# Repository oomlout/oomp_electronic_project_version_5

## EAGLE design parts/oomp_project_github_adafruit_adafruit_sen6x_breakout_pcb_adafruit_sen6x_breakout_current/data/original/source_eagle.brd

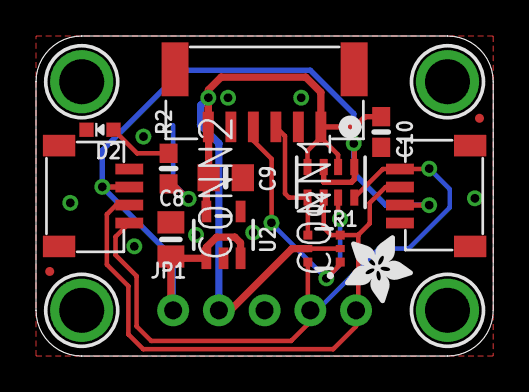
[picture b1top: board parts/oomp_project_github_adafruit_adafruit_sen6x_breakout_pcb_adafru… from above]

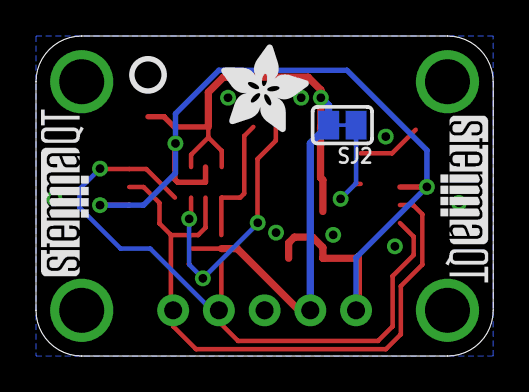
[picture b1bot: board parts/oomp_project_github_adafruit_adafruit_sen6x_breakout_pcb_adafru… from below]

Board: 2 copper layers, 25.4 x 17.8 mm, 35 parts (8 on the bottom side), 9 nets.

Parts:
C8, C9: 10uF; 0805-NO
C10: 0.1uF; 0603-NO
CONN1, CONN2: STEMMA_I2C_QT; JST_SH4
D2: GREEN; CHIPLED_0603_NOOUTLINE
FID1, FID2: FIDUCIAL_0.5MM
JP1: 1X05_ROUND_70
PLABEL14: PLABEL14
PLABEL15: PLABEL15
PLABEL16: PLABEL16
PLABEL17: PLABEL17
PLABEL18: PLABEL18
PLABEL19: PLABEL19
PLABEL20: PLABEL20
PLABEL21: PLABEL21
PLABEL22: PLABEL22
PLABEL23: PLABEL23
PLABEL24: PLABEL24
Q2: BSS138; SOT363
R1: 10K Pack; RESPACK_4X0603
R2: 10K; 0603-NO
SJ2: SOLDERJUMPER_CLOSEDWIRE
U2: AP2127K-3.3; SOT23-5
U$2: ADAFRUIT_5MM
U$35, U$36, U$38, U$39: MOUNTINGHOLE2.5; MOUNTINGHOLE_2.5_PLATED
U$41: ADAFRUIT_3.5MM
U$42: PCBFEAT-REV-040
U$43, U$44: STEMMAQT
X1: SM06B-GHS-TB; CONN_SM06B-GHS-TB_JST

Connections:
3.3V: C9.1, C10.1, JP1.2, Q2.2, Q2.5, R1.2, R1.4, SJ2.2, U2.5, X1.1, X1.6
GND: C8.2, C9.2, C10.2, CONN1.1, CONN1.MT1, CONN1.MT2, CONN2.1, CONN2.MT1, CONN2.MT2, D2.C, JP1.3, U2.2, X1.2, X1.5
unnamed: D2.A, R2.2
unnamed: R2.1, SJ2.1
SCL: CONN1.4, CONN2.4, JP1.4, Q2.6, R1.8
SCL_3V: Q2.1, R1.7, X1.4
SDA: CONN1.3, CONN2.3, JP1.5, Q2.3, R1.6
SDA_3V: Q2.4, R1.5, X1.3
VCC: C8.1, CONN1.2, CONN2.2, JP1.1, R1.1, R1.3, U2.1, U2.3

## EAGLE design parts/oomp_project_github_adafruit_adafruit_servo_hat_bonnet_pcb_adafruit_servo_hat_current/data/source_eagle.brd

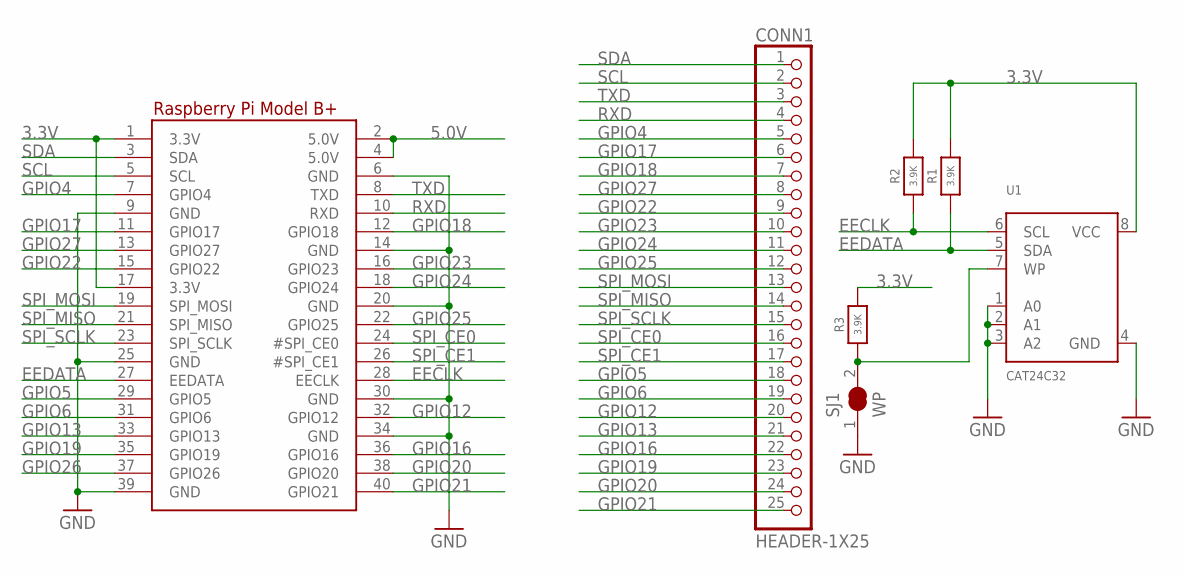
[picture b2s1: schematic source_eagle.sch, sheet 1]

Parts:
CONN1: HEADER-1X25; 1X25_ROUND_70MIL
R1, R2, R3: 3.9K; 0805-NO
RPI1: RASPBERRYPI_BPLUS_HATSLOTS; PI_HAT_SLOTS
SJ1: WP; SOLDERJUMPER_CLOSEDWIRE
U1: CAT24C32; SOIC8_150MIL

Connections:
3.3V: R1.2, R2.2, R3.2, RPI1.1 (3.3V), RPI1.17 (3.3V), U1.8 (VCC); also elsewhere on the board
5.0V: RPI1.2 (5.0V), RPI1.4 (5.0V)
EECLK: R2.1, RPI1.28 (EECLK), U1.6 (SCL)
EEDATA: R1.1, RPI1.27 (EEDATA), U1.5 (SDA)
GND: RPI1.6 (GND), RPI1.9 (GND), RPI1.14 (GND), RPI1.20 (GND), RPI1.25 (GND), RPI1.30 (GND), RPI1.34 (GND), RPI1.39 (GND), SJ1.1, U1.1 (A0), U1.2 (A1), U1.3 (A2), U1.4 (GND); also elsewhere on the board
GPIO4: CONN1.5, RPI1.7 (GPIO4)
GPIO5: CONN1.18, RPI1.29 (GPIO5)
GPIO6: CONN1.19, RPI1.31 (GPIO6)
GPIO12: CONN1.20, RPI1.32 (GPIO12)
GPIO13: CONN1.21, RPI1.33 (GPIO13)
GPIO16: CONN1.22, RPI1.36 (GPIO16)
GPIO17: CONN1.6, RPI1.11 (GPIO17)
GPIO18: CONN1.7, RPI1.12 (GPIO18)
GPIO19: CONN1.23, RPI1.35 (GPIO19)
GPIO20: CONN1.24, RPI1.38 (GPIO20)
GPIO21: CONN1.25, RPI1.40 (GPIO21)
GPIO22: CONN1.9, RPI1.15 (GPIO22)
GPIO23: CONN1.10, RPI1.16 (GPIO23)
GPIO24: CONN1.11, RPI1.18 (GPIO24)
GPIO25: CONN1.12, RPI1.22 (GPIO25)
GPIO26: RPI1.37 (GPIO26)
GPIO27: CONN1.8, RPI1.13 (GPIO27)
unnamed: R3.1, SJ1.2, U1.7 (WP)
RXD: CONN1.4, RPI1.10 (RXD)
SCL: CONN1.2, RPI1.5 (SCL); also elsewhere on the board
SDA: CONN1.1, RPI1.3 (SDA); also elsewhere on the board
SPI_CE0: CONN1.16, RPI1.24 (#SPI_CE0)
SPI_CE1: CONN1.17, RPI1.26 (#SPI_CE1)
SPI_MISO: CONN1.14, RPI1.21 (SPI_MISO)
SPI_MOSI: CONN1.13, RPI1.19 (SPI_MOSI)
SPI_SCLK: CONN1.15, RPI1.23 (SPI_SCLK)
TXD: CONN1.3, RPI1.8 (TXD)

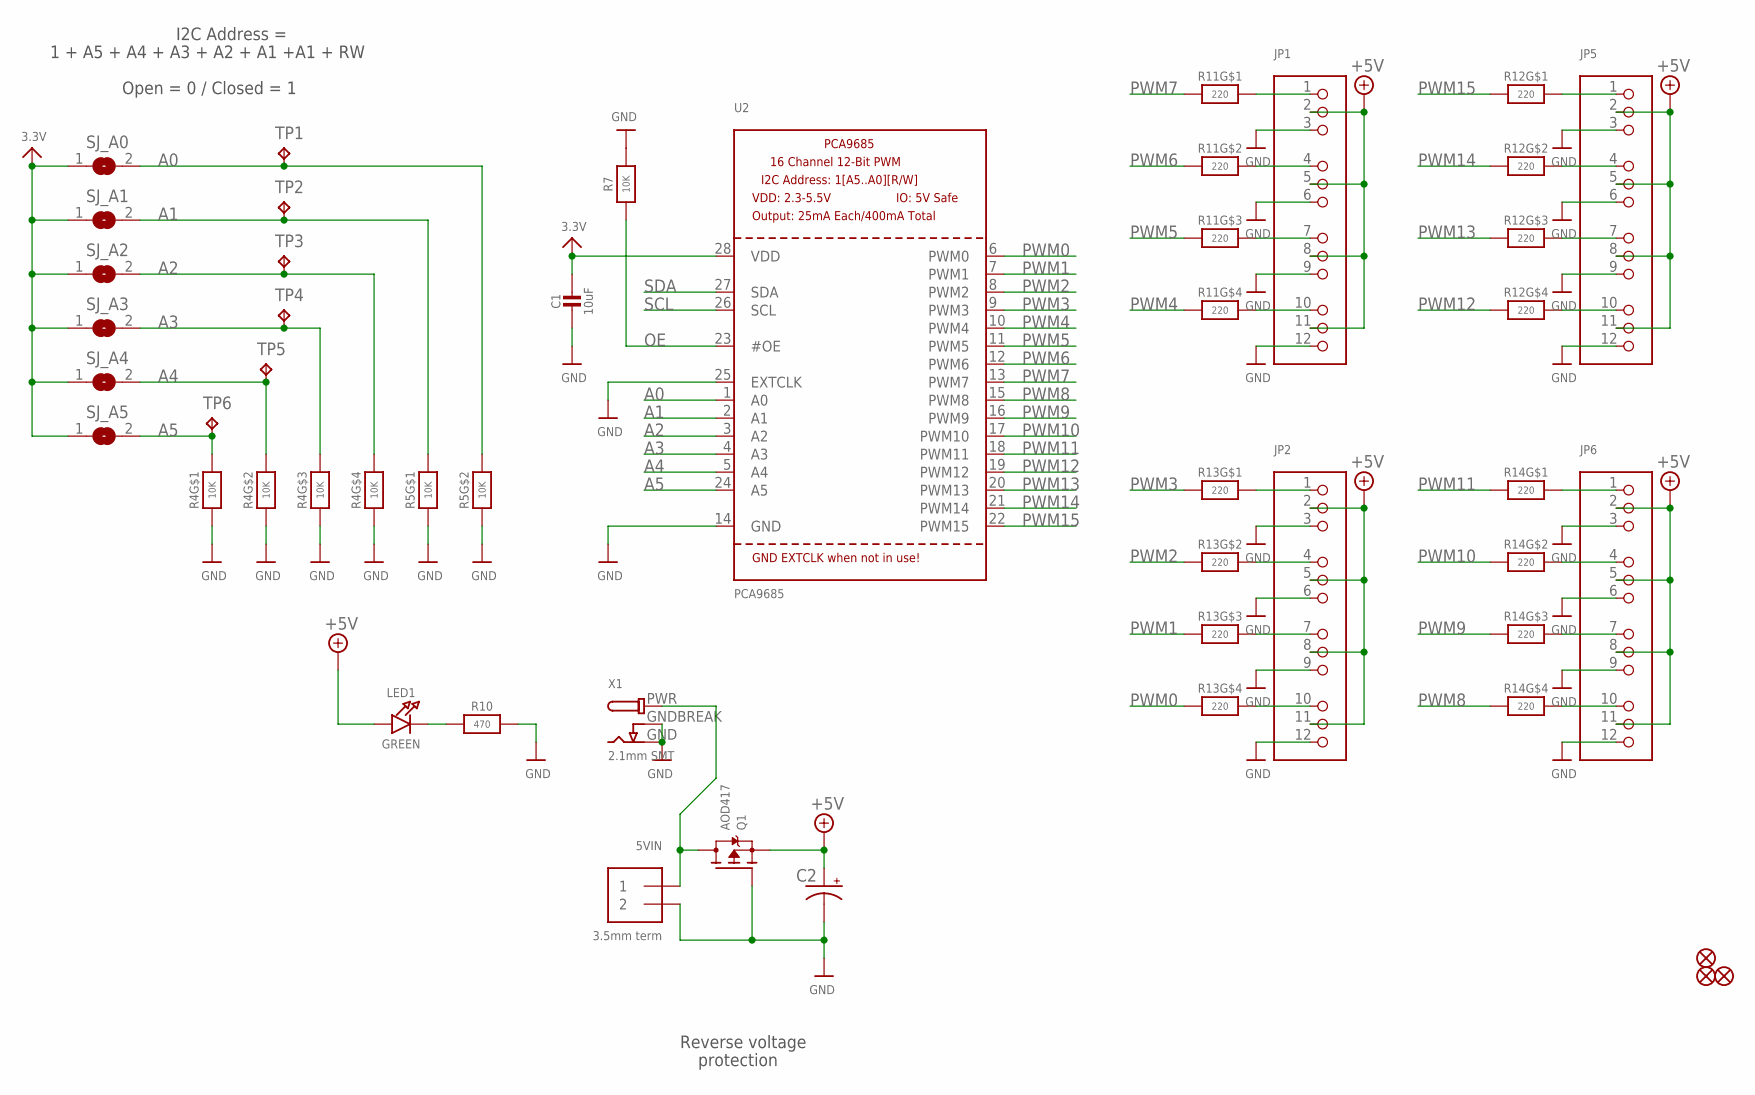
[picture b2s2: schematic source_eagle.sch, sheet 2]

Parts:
5VIN: 3.5mm term; TERMBLOCK_1X2-3.5MM
C1: 10uF; 0805-NO
C2: CPOL-USE3.5-8; E3,5-8
FID1, FID2, FID3: FIDUCIAL""; FIDUCIAL_1MM
JP1, JP2, JP5, JP6: HEADER-3X04; 3X04
LED1: GREEN; CHIPLED_0805_NOOUTLINE
Q1: AOD417; TO252
R4, R5: 10K; RESPACK_4X0603
R7: 10K; 0805-NO
R10: 470; _0805MP
R11, R12, R13, R14: 220; RESPACK_4X0603
SJ_A0, SJ_A1, SJ_A2, SJ_A3, SJ_A4, SJ_A5: SOLDERJUMPERREFLOW_NOPASTE; SOLDERJUMPER_REFLOW_NOPASTE
TP1, TP2, TP3, TP4, TP5, TP6: TPB1,27; B1,27
U2: PCA9685; TSSOP28
X1: 2.1mm SMT; DCJACK_2MM_SMT

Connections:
3.3V: C1.1, SJ_A0.1, SJ_A1.1, SJ_A2.1, SJ_A3.1, SJ_A4.1, SJ_A5.1, U2.28 (VDD); also elsewhere on the board
+5V: C2.+, JP1.2, JP1.5, JP1.8, JP1.11, JP2.2, JP2.5, JP2.8, JP2.11, JP5.2, JP5.5, JP5.8, JP5.11, JP6.2, JP6.5, JP6.8, JP6.11, LED1.A, Q1.2 (S)
A0: R5.7 (2), SJ_A0.2, TP1.TP, U2.1 (A0)
A1: R5.8 (2), SJ_A1.2, TP2.TP, U2.2 (A1)
A2: R4.5 (2), SJ_A2.2, TP3.TP, U2.3 (A2)
A3: R4.6 (2), SJ_A3.2, TP4.TP, U2.4 (A3)
A4: R4.7 (2), SJ_A4.2, TP5.TP, U2.5 (A4)
A5: R4.8 (2), SJ_A5.2, TP6.TP, U2.24 (A5)
GND: 5VIN.2, C1.2, C2.-, JP1.3, JP1.6, JP1.9, JP1.12, JP2.3, JP2.6, JP2.9, JP2.12, JP5.3, JP5.6, JP5.9, JP5.12, JP6.3, JP6.6, JP6.9, JP6.12, Q1.1 (G), R4.1, R4.2 (1), R4.3 (1), R4.4 (1), R5.1, R5.2 (1), R7.2, R10.2, U2.14 (GND), U2.25 (EXTCLK), X1.GND, X1.GNDBREAK; also elsewhere on the board
unnamed: LED1.C, R10.1
unnamed: JP1.4, R11.7 (2)
unnamed: JP1.1, R11.8 (2)
unnamed: JP1.7, R11.6 (2)
unnamed: JP1.10, R11.5 (2)
unnamed: JP2.1, R13.8 (2)
unnamed: JP2.4, R13.7 (2)
unnamed: JP2.7, R13.6 (2)
unnamed: JP2.10, R13.5 (2)
unnamed: JP6.10, R14.5 (2)
unnamed: JP6.7, R14.6 (2)
unnamed: JP6.4, R14.7 (2)
unnamed: JP6.1, R14.8 (2)
unnamed: JP5.10, R12.5 (2)
unnamed: JP5.7, R12.6 (2)
unnamed: JP5.4, R12.7 (2)
unnamed: JP5.1, R12.8 (2)
OE: R7.1, U2.23 (#OE)
PWM0: R13.4 (1), U2.6 (PWM0)
PWM1: R13.3 (1), U2.7 (PWM1)
PWM2: R13.2 (1), U2.8 (PWM2)
PWM3: R13.1, U2.9 (PWM3)
PWM4: R11.4 (1), U2.10 (PWM4)
PWM5: R11.3 (1), U2.11 (PWM5)
PWM6: R11.2 (1), U2.12 (PWM6)
PWM7: R11.1, U2.13 (PWM7)
PWM8: R14.4 (1), U2.15 (PWM8)
PWM9: R14.3 (1), U2.16 (PWM9)
PWM10: R14.2 (1), U2.17 (PWM10)
PWM11: R14.1, U2.18 (PWM11)
PWM12: R12.4 (1), U2.19 (PWM12)
PWM13: R12.3 (1), U2.20 (PWM13)
PWM14: R12.2 (1), U2.21 (PWM14)
PWM15: R12.1, U2.22 (PWM15)
PWRIN: 5VIN.1, Q1.3 (D), X1.PWR
SCL: U2.26 (SCL); also elsewhere on the board
SDA: U2.27 (SDA); also elsewhere on the board

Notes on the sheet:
Reverse voltage
protection
1 + A5 + A4 + A3 + A2 + A1 +A1 + RW
I2C Address =
Open = 0 / Closed = 1

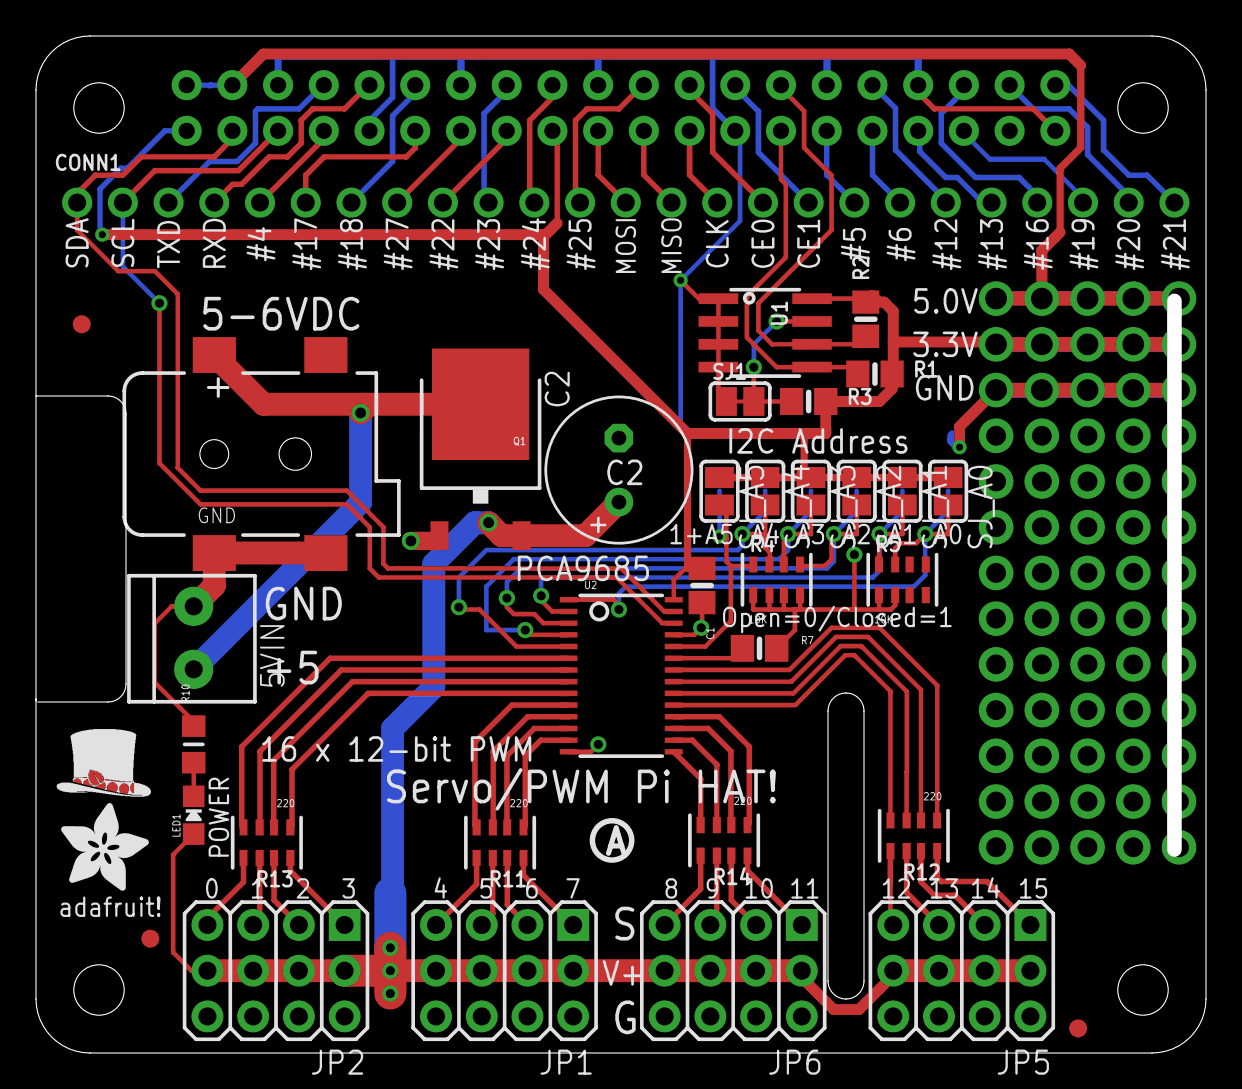
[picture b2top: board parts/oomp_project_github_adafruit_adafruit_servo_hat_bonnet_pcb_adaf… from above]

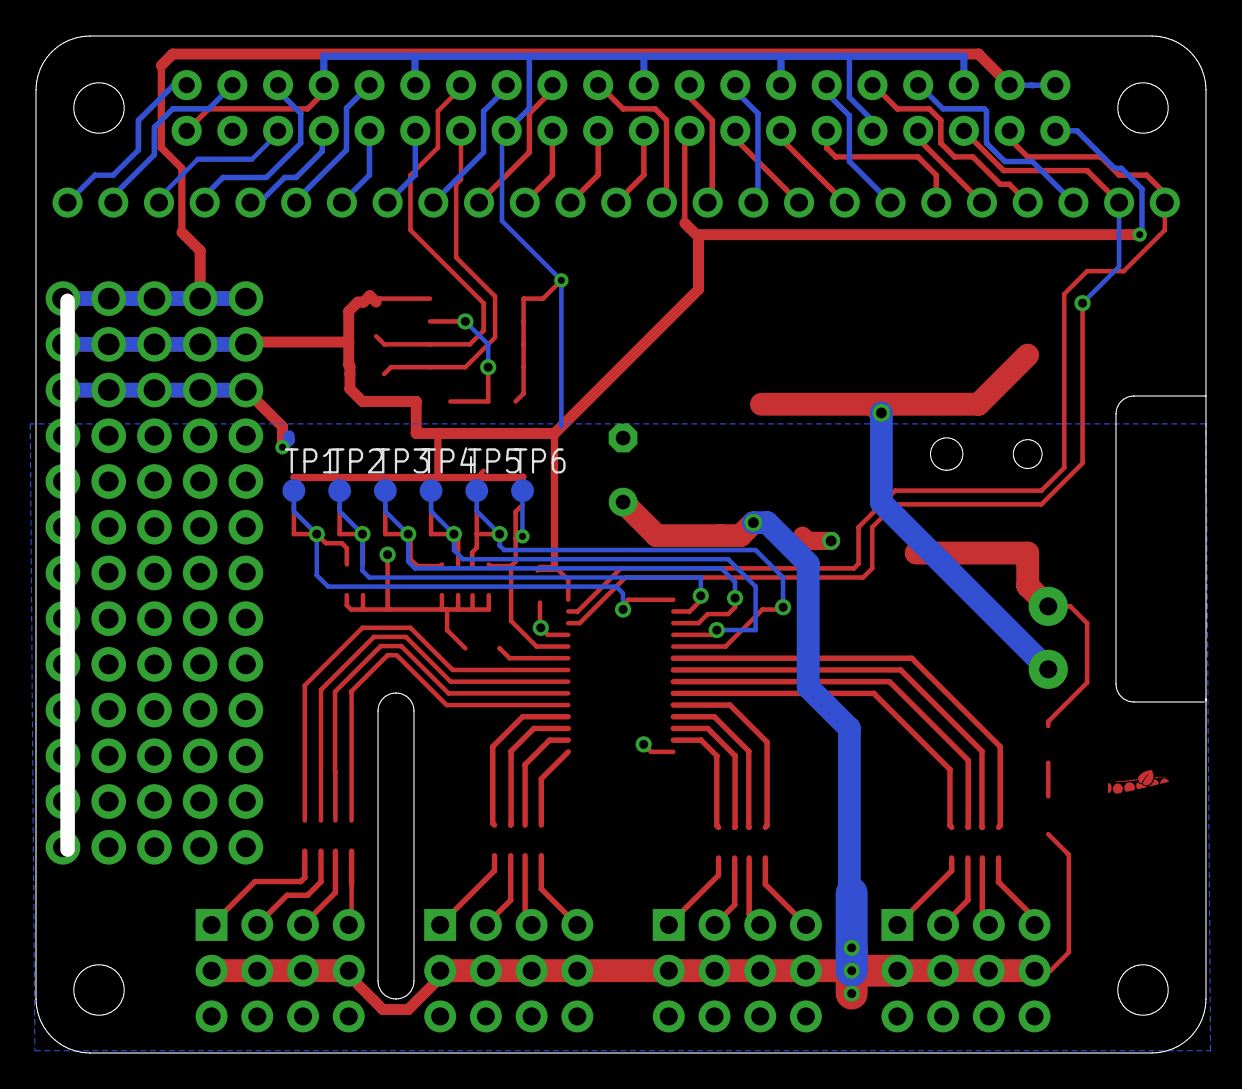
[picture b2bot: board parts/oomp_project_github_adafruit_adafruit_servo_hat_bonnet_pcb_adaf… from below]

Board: 2 copper layers, 65.0 x 56.5 mm, 44 parts (6 on the bottom side), 73 nets.

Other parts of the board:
U$5: PIHATLOGO
U$6: PCBFEAT-REV-056
U$51: ADAFRUIT_5MM

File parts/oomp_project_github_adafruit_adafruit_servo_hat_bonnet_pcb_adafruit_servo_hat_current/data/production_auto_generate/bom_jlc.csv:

Comment,Designator,Footprint,LCSC Part #
,"JP1,JP2,JP5,JP6",Adafruit Servo HAT rev A-import-fps:3X04,
,U$51,Adafruit Servo HAT rev A-import-fps:ADAFRUIT_5MM,
,C2,"Adafruit Servo HAT rev A-import-fps:E3,5-8",
,U$6,Adafruit Servo HAT rev A-import-fps:PCBFEAT-REV-056,
,U$5,Adafruit Servo HAT rev A-import-fps:PIHATLOGO,
10K,R7,Adafruit Servo HAT rev A-import-fps:0805-NO,C17414
10K,"R4,R5",Adafruit Servo HAT rev A-import-fps:RESPACK_4X0603,C98220
10uF,C1,Adafruit Servo HAT rev A-import-fps:0805-NO,
2.1mm SMT,X1,Adafruit Servo HAT rev A-import-fps:DCJACK_2MM_SMT,
220,"R11,R12,R13,R14",Adafruit Servo HAT rev A-import-fps:RESPACK_4X0603,C2907127
3.5mm term,UNK5VIN0,Adafruit Servo HAT rev A-import-fps:TERMBLOCK_1X2-3.5MM,
3.9K,"R1,R2,R3",Adafruit Servo HAT rev A-import-fps:0805-NO,C2907252
470,R10,Adafruit Servo HAT rev A-import-fps:_0805MP,C17710
AOD417,Q1,Adafruit Servo HAT rev A-import-fps:TO252,
CAT24C32,U1,Adafruit Servo HAT rev A-import-fps:SOIC8_150MIL,
GREEN,LED1,Adafruit Servo HAT rev A-import-fps:CHIPLED_0805_NOOUTLINE,
HEADER-1X25,CONN1,Adafruit Servo HAT rev A-import-fps:1X25_ROUND_70MIL,C2883713
PCA9685,U2,Adafruit Servo HAT rev A-import-fps:TSSOP28,
RASPBERRYPI_BPLUS_HATSLOTS,RPI1,Adafruit Servo HAT rev A-import-fps:PI_HAT_SLOTS,
"TPB1,27","TP1,TP2,TP3,TP4,TP5,TP6","Adafruit Servo HAT rev A-import-fps:B1,27",

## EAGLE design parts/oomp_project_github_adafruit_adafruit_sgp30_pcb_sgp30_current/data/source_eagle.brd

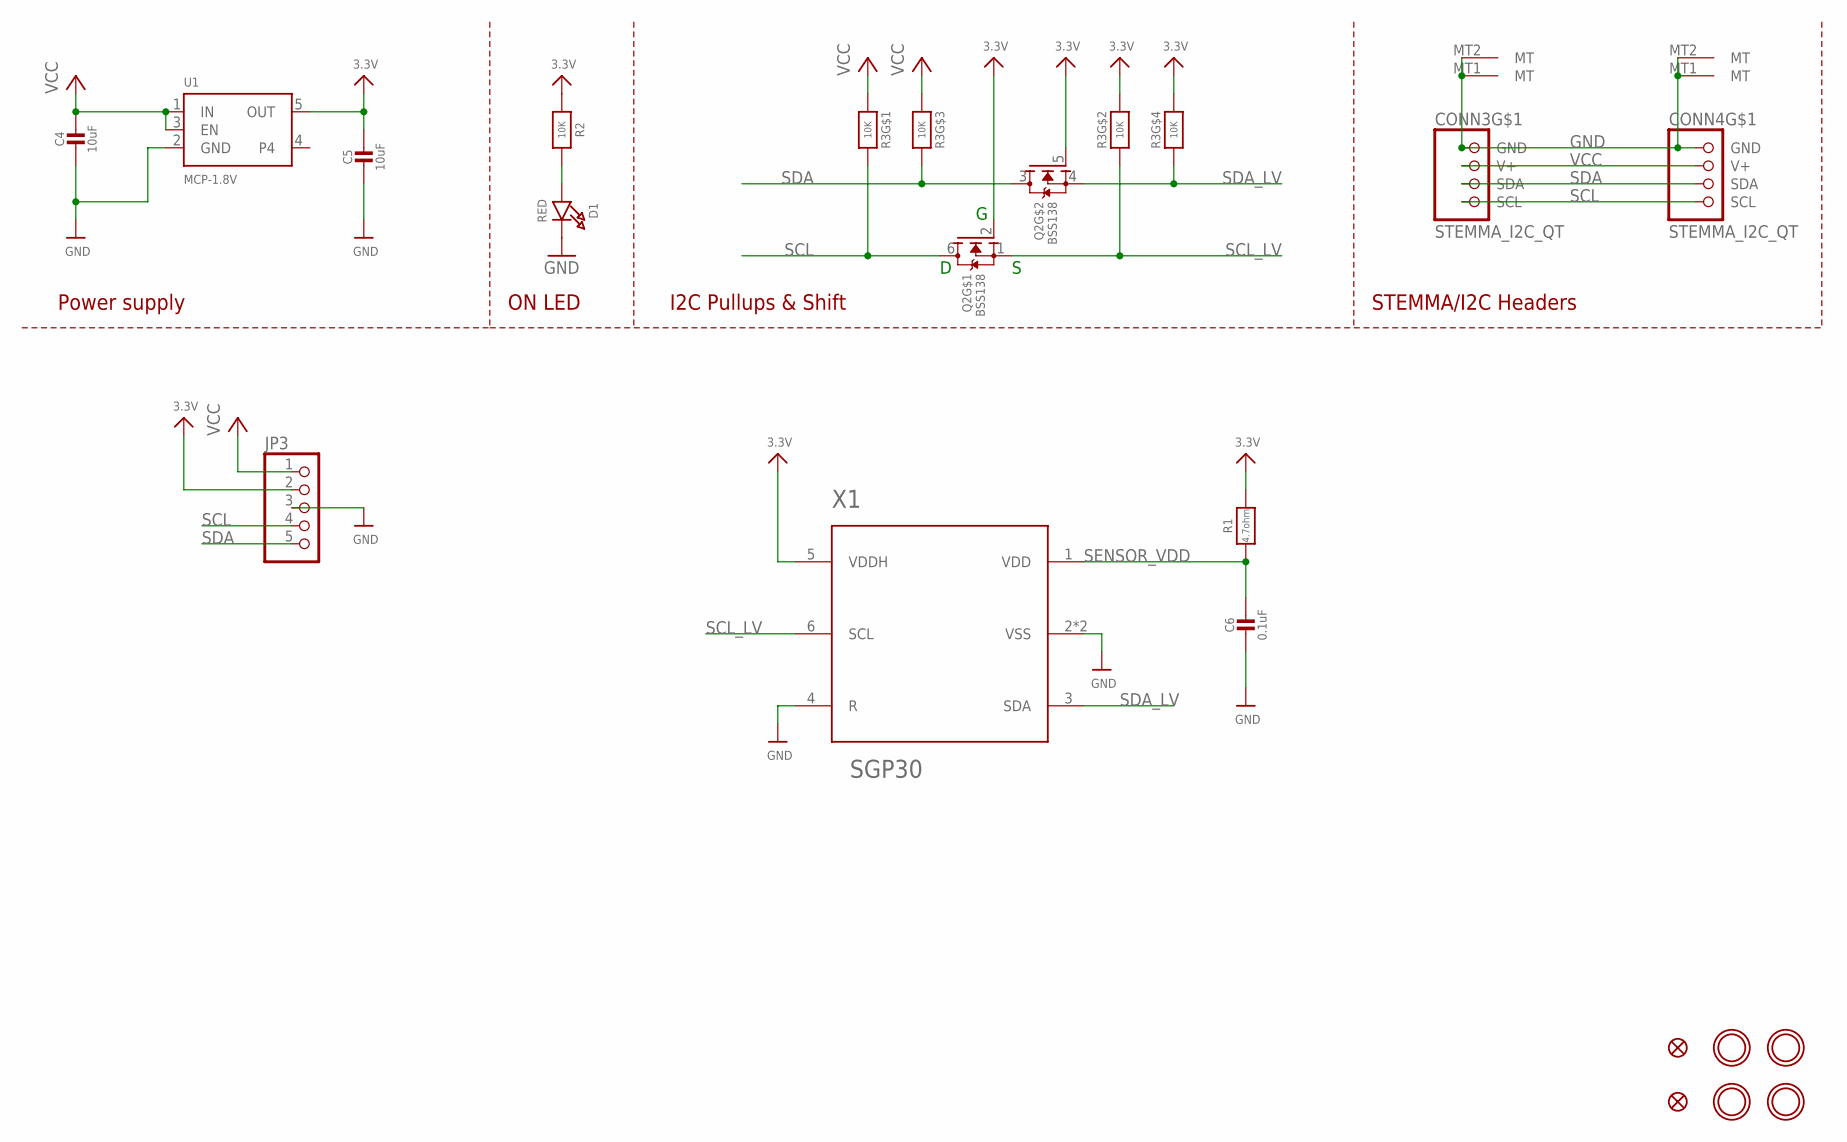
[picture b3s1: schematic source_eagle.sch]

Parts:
C4, C5: 10uF; 0805-NO
C6: 0.1uF; 0603-NO
CONN3, CONN4: STEMMA_I2C_QT; JST_SH4
D1: RED; CHIPLED_0603_NOOUTLINE
FID3, FID4: FIDUCIAL_1MM
JP3: HEADER-1X570MIL; 1X05_ROUND_70
Q2: BSS138; SOT363
R1: 4.7ohm; 0603-NO
R2: 10K; 0603-NO
R3: 10K; RESPACK_4X0603
U1: MCP-1.8V; SOT23-5
U$28, U$29, U$31, U$32: MOUNTINGHOLE2.5; MOUNTINGHOLE_2.5_PLATED
X1: SGP30

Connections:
3.3V: C5.1, JP3.2, Q2.2 (G), Q2.5 (G), R1.2, R2.1, R3.2 (1), R3.4 (1), U1.5 (OUT), X1.5 (VDDH)
GND: C4.2, C5.2, C6.2, CONN3.1 (GND), CONN3.MT1 (MT), CONN3.MT2 (MT), CONN4.1 (GND), CONN4.MT1 (MT), CONN4.MT2 (MT), D1.C, JP3.3, U1.2 (GND), X1.2 (VSS), X1.4 (R), X1.P$7 (VSS)
unnamed: D1.A, R2.2
SCL: CONN3.4 (SCL), CONN4.4 (SCL), JP3.4, Q2.6 (D), R3.8 (2)
SCL_LV: Q2.1 (S), R3.7 (2), X1.6 (SCL)
SDA: CONN3.3 (SDA), CONN4.3 (SDA), JP3.5, Q2.3 (D), R3.6 (2)
SDA_LV: Q2.4 (S), R3.5 (2), X1.3 (SDA)
SENSOR_VDD: C6.1, R1.1, X1.1 (VDD)
VCC: C4.1, CONN3.2 (V+), CONN4.2 (V+), JP3.1, R3.1, R3.3 (1), U1.1 (IN), U1.3 (EN)

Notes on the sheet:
I2C Pullups & Shift
STEMMA/I2C Headers
ON LED
Power supply

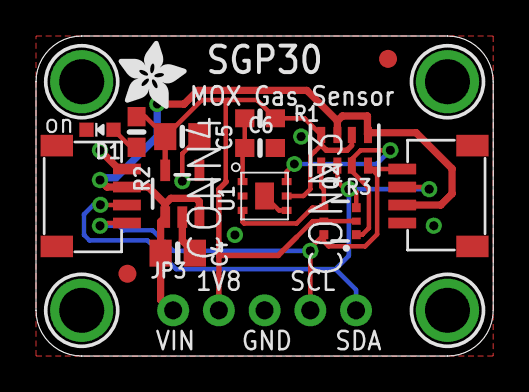
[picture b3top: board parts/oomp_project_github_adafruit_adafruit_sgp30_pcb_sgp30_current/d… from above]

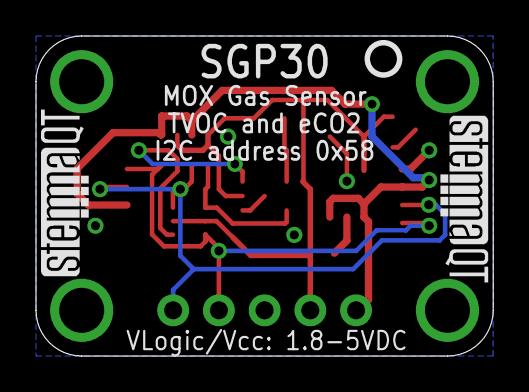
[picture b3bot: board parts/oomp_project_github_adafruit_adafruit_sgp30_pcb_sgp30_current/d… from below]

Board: 2 copper layers, 25.4 x 17.8 mm, 23 parts (3 on the bottom side), 9 nets.

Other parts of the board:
U$34: ADAFRUIT_3.5MM
U$35: PCBFEAT-REV-040
U$36, U$37: STEMMAQT

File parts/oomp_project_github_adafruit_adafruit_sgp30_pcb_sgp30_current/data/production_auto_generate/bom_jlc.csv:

Comment,Designator,Footprint,LCSC Part #
,JP3,SGP30 Rev D-import-fps:1X05_ROUND_70,C42431835
,U$34,SGP30 Rev D-import-fps:ADAFRUIT_3.5MM,
,U$35,SGP30 Rev D-import-fps:PCBFEAT-REV-040,
,"U$36,U$37",SGP30 Rev D-import-fps:STEMMAQT,
0.1uF,C6,SGP30 Rev D-import-fps:0603-NO,C14663
10K,R2,SGP30 Rev D-import-fps:0603-NO,C98220
10K,R3,SGP30 Rev D-import-fps:RESPACK_4X0603,C98220
10uF,"C4,C5",SGP30 Rev D-import-fps:0805-NO,
4.7ohm,R1,SGP30 Rev D-import-fps:0603-NO,
BSS138,Q2,SGP30 Rev D-import-fps:SOT363,
MCP-1.8V,U1,SGP30 Rev D-import-fps:SOT23-5,
RED,D1,SGP30 Rev D-import-fps:CHIPLED_0603_NOOUTLINE,
SGP30,X1,SGP30 Rev D-import-fps:SGP30,
STEMMA_I2C_QT,"CONN3,CONN4",SGP30 Rev D-import-fps:JST_SH4,C160404

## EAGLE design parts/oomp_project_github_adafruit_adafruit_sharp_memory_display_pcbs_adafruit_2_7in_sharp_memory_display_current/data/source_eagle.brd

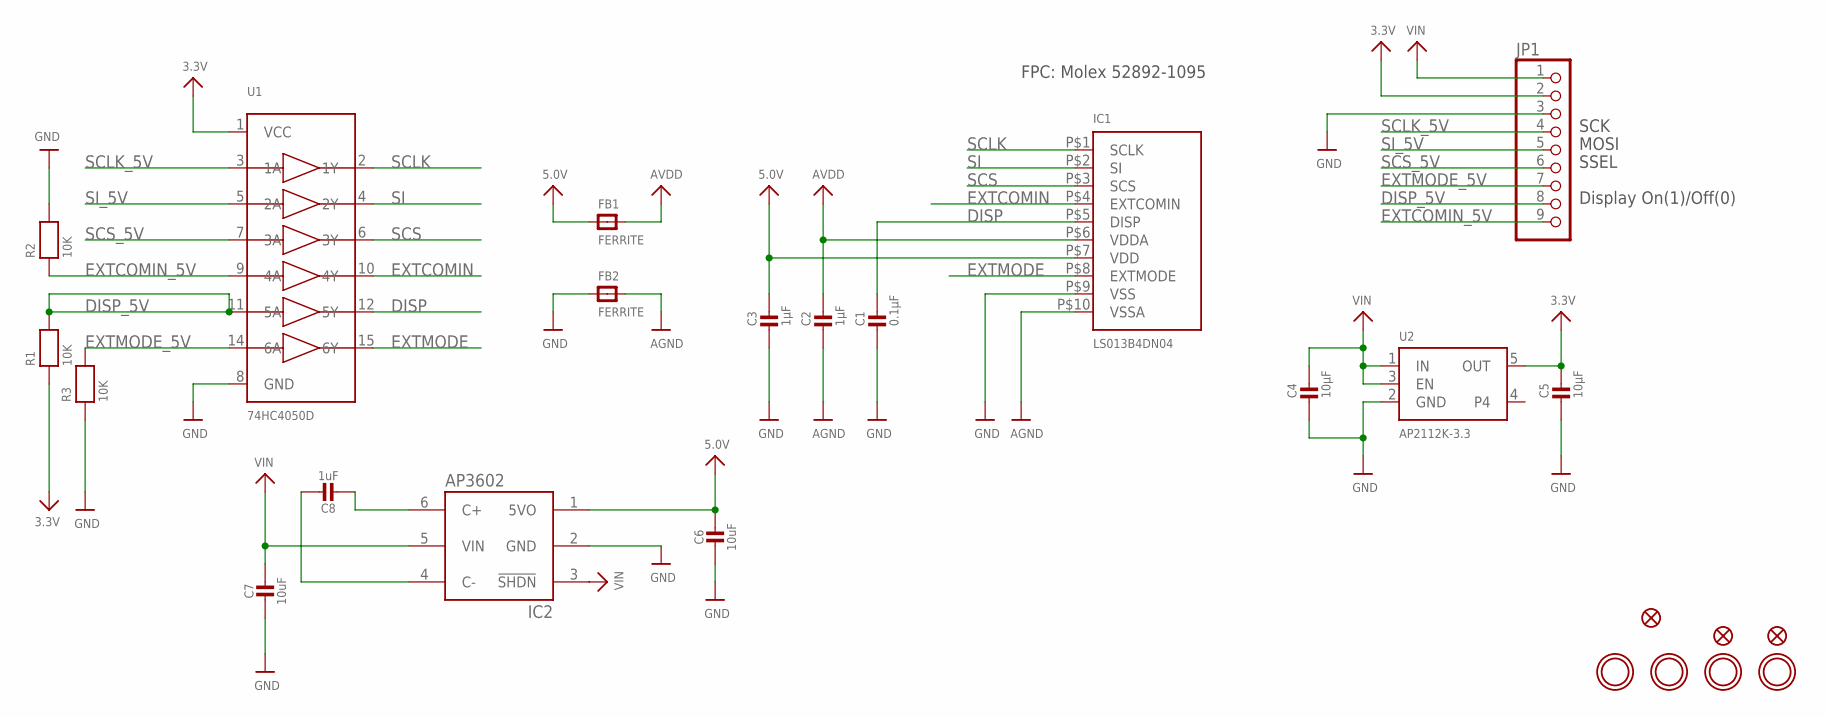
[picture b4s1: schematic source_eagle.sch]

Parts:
C1: 0.1µF; 0603-NO
C2: 1µF; 0805_10MGAP
C3: 1µF; 0805-NO
C4, C5: 10µF; 0805-NO
C6, C7: 10uF; 0805-NO
C8: 1uF; 0805-NO
FB1, FB2: FERRITE; _0805
FID1, FID2, FID3: FIDUCIAL_1MM
IC1: LS013B4DN04; SHARP_2.7IN
IC2: AP3602; SOT23-6
JP1: HEADER-1X970MIL; 1X09_ROUND_70
R1, R2, R3: 10K; 0603-NO
U1: 74HC4050D; SOIC16
U2: AP2112K-3.3; SOT23-5
U$21, U$22: MOUNTINGHOLE2.5_THICK; MOUNTINGHOLE_2.5_PLATED_THICK
U$27, U$28: MOUNTINGHOLE2.5; MOUNTINGHOLE_2.5_PLATED

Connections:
3.3V: C5.1, JP1.2, R1.1, U1.1 (VCC), U2.5 (OUT)
5.0V: C3.1, C6.1, FB1.1, IC1.P$7 (VDD), IC2.1 (5VO)
AGND: C2.2, FB2.2, IC1.P$10 (VSSA)
AVDD: C2.1, FB1.2, IC1.P$6 (VDDA)
DISP: C1.1, IC1.P$5 (DISP), U1.12 (5Y)
DISP_5V: JP1.8, R1.2, U1.11 (5A)
EXTCOMIN: IC1.P$4 (EXTCOMIN), U1.10 (4Y)
EXTCOMIN_5V: JP1.9, R2.1, U1.9 (4A)
EXTMODE: IC1.P$8 (EXTMODE), U1.15 (6Y)
EXTMODE_5V: JP1.7, R3.2, U1.14 (6A)
GND: C1.2, C3.2, C4.2, C5.2, C6.2, C7.2, FB2.1, IC1.P$9 (VSS), IC2.2 (GND), JP1.3, R2.2, R3.1, U1.8 (GND), U2.2 (GND)
unnamed: C8.2, IC2.6 (C+)
unnamed: C8.1, IC2.4 (C-)
SCLK: IC1.P$1 (SCLK), U1.2 (1Y)
SCLK_5V: JP1.4, U1.3 (1A)
SCS: IC1.P$3 (SCS), U1.6 (3Y)
SCS_5V: JP1.6, U1.7 (3A)
SI: IC1.P$2 (SI), U1.4 (2Y)
SI_5V: JP1.5, U1.5 (2A)
VIN: C4.1, C7.1, IC2.3 (!SHDN), IC2.5 (VIN), JP1.1, U2.1 (IN), U2.3 (EN)

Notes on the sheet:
SSEL
MOSI
SCK
Display On(1)/Off(0)
FPC: Molex 52892-1095

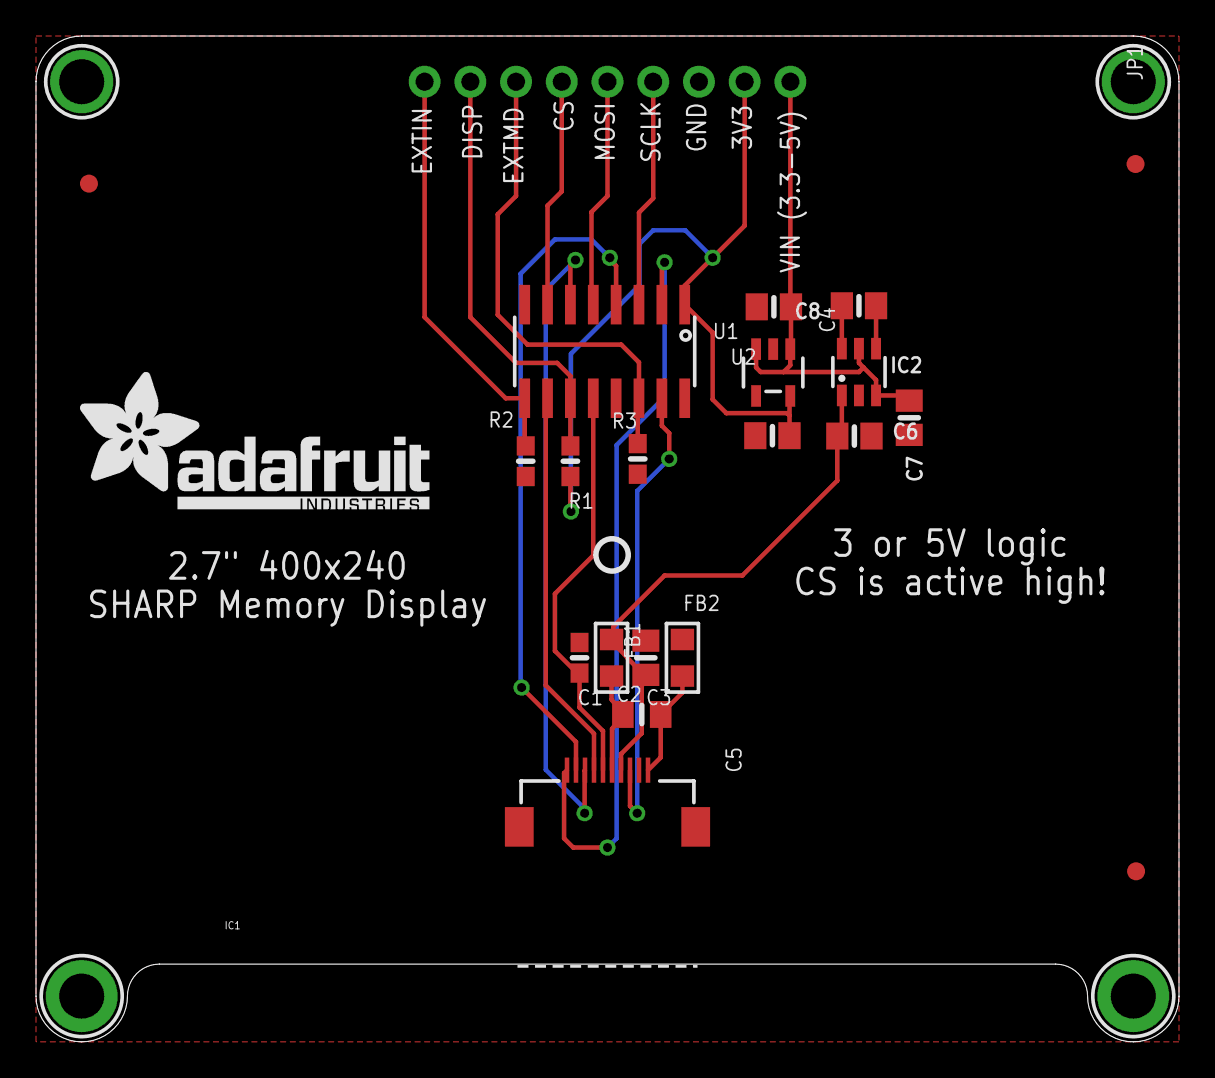
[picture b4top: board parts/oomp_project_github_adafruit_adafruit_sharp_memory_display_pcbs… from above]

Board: 2 copper layers, 63.5 x 55.9 mm, 27 parts (0 on the bottom side), 20 nets.

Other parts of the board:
U$29: PCBFEAT-REV-040
U$32: ADAFRUIT_TEXT_20MM

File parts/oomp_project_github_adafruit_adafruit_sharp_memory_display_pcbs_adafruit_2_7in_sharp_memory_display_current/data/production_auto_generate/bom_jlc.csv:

Comment,Designator,Footprint,LCSC Part #
,JP1,Adafruit 2.7in Sharp Memory Display-import-fps:1X09_ROUND_70,C2932701
,U$32,Adafruit 2.7in Sharp Memory Display-import-fps:ADAFRUIT_TEXT_20MM,
,U$29,Adafruit 2.7in Sharp Memory Display-import-fps:PCBFEAT-REV-040,
0.1µF,C1,Adafruit 2.7in Sharp Memory Display-import-fps:0603-NO,C14663
10K,"R1,R2,R3",Adafruit 2.7in Sharp Memory Display-import-fps:0603-NO,C98220
10uF,"C6,C7",Adafruit 2.7in Sharp Memory Display-import-fps:0805-NO,
10µF,"C4,C5",Adafruit 2.7in Sharp Memory Display-import-fps:0805-NO,
1uF,C8,Adafruit 2.7in Sharp Memory Display-import-fps:0805-NO,
1µF,C3,Adafruit 2.7in Sharp Memory Display-import-fps:0805-NO,
1µF,C2,Adafruit 2.7in Sharp Memory Display-import-fps:0805_10MGAP,
74HC4050D,U1,Adafruit 2.7in Sharp Memory Display-import-fps:SOIC16,
AP2112K-3.3,U2,Adafruit 2.7in Sharp Memory Display-import-fps:SOT23-5,
AP3602,IC2,Adafruit 2.7in Sharp Memory Display-import-fps:SOT23-6,
FERRITE,"FB1,FB2",Adafruit 2.7in Sharp Memory Display-import-fps:_0805,
LS013B4DN04,IC1,Adafruit 2.7in Sharp Memory Display-import-fps:SHARP_2.7IN,

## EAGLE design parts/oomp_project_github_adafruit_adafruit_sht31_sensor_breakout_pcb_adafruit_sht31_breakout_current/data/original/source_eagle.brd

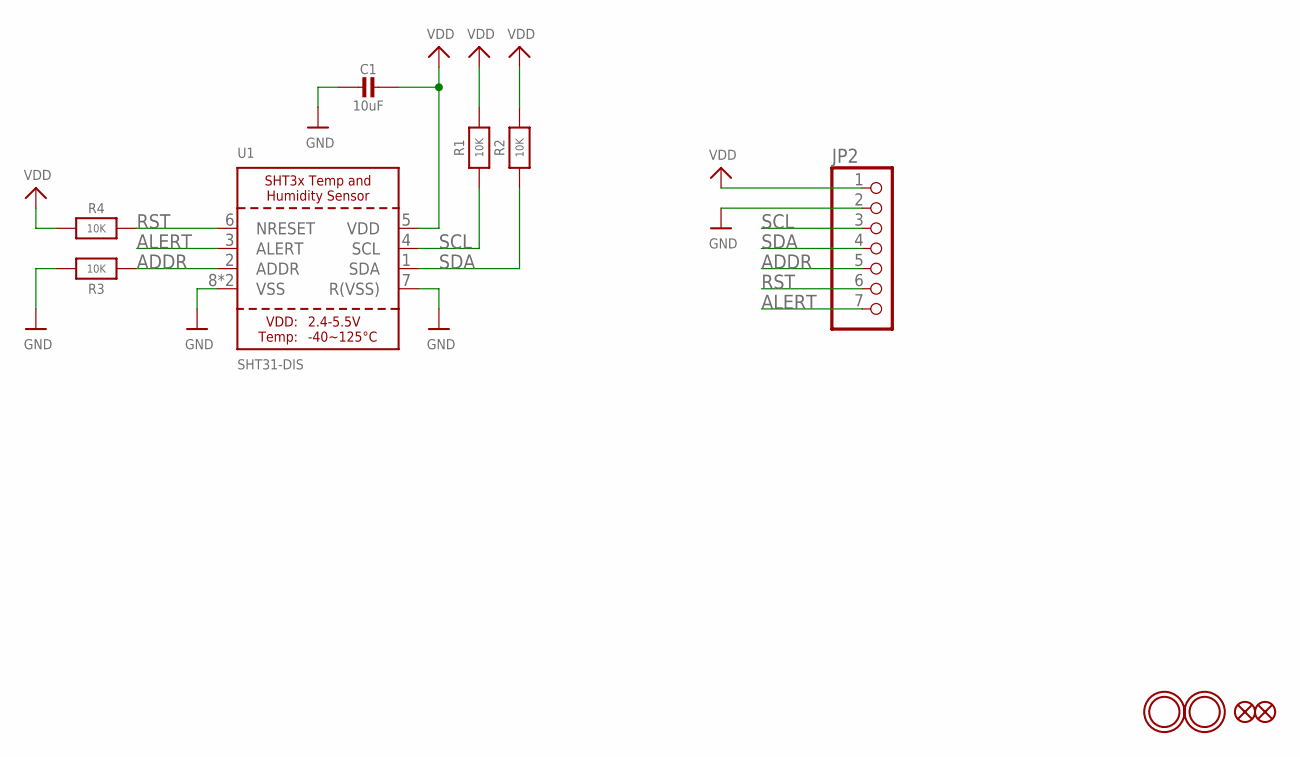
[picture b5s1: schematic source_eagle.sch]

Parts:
C1: 10uF; 0805-NO
FID2, FID3: FIDUCIAL""; FIDUCIAL_1MM
JP2: HEADER-1X770MIL; 1X07_ROUND_70
R1, R2, R4: 10K; 0805-NO
R3: 10K; _0805MP
U1: SHT31-DIS; SHT3X
U$1, U$2: MOUNTINGHOLE2.5; MOUNTINGHOLE_2.5_PLATED

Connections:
ADDR: JP2.5, R3.1, U1.2 (ADDR)
ALERT: JP2.7, U1.3 (ALERT)
GND: C1.2, JP2.2, R3.2, U1.7 (R(VSS)), U1.8 (VSS), U1.THERMAL (VSS)
RST: JP2.6, R4.2, U1.6 (NRESET)
SCL: JP2.3, R1.1, U1.4 (SCL)
SDA: JP2.4, R2.1, U1.1 (SDA)
VDD: C1.1, JP2.1, R1.2, R2.2, R4.1, U1.5 (VDD)

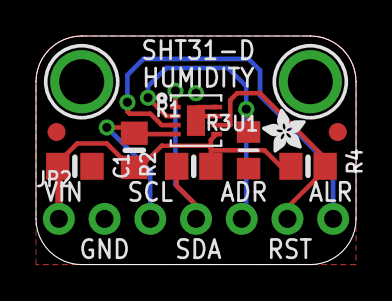
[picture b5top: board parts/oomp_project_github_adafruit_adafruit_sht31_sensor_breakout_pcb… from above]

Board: 2 copper layers, 17.8 x 12.7 mm, 13 parts (1 on the bottom side), 7 nets.

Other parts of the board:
U$11: PCBFEAT-REV-040
U$13: ADAFRUIT_2.5MM

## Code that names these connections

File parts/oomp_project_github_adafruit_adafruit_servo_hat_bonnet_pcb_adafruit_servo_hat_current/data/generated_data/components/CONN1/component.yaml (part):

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      position:
        x: 172.72
        y: 83.82
      net: GPIO4
      net_aliases:
      - GPIO4
      net_scope: global
      no_connect: false
      connected_to:
      - reference: RPI1
        pin_number: '7'
        pin_name: GPIO4
    - number: '6'
      name: '6'
      electrical_type: passive
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      position:
        x: 172.72
        y: 86.36
      net: GPIO17
      net_aliases:
      - GPIO17
      net_scope: global
      no_connect: false
      connected_to:
      - reference: RPI1
        pin_number: '11'
        pin_name: GPIO17
    - number: '7'
      name: '7'
      electrical_type: passive
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      position:
        x: 172.72
        y: 88.9
      net: GPIO18
      net_aliases:
      - GPIO18
      net_scope: global
      no_connect: false
      connected_to:
      - reference: RPI1
        pin_number: '12'
        pin_name: GPIO18
    - number: '8'
      name: '8'
      electrical_type: passive
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      position:
        x: 172.72
        y: 91.44
      net: GPIO27
      net_aliases:
      - GPIO27
      net_scope: global
      no_connect: false
      connected_to:
      - reference: RPI1
        pin_number: '13'
        pin_name: GPIO27
    - number: '9'
      name: '9'
      electrical_type: passive
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      position:
        x: 172.72
        y: 93.98
      net: GPIO22
      net_aliases:
      - GPIO22
      net_scope: global
      no_connect: false
      connected_to:
      - reference: RPI1
        pin_number: '15'
        pin_name: GPIO22
    - number: '10'
      name: '10'
      electrical_type: passive
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      position:
        x: 172.72
        y: 96.52
      net: GPIO23
      net_aliases:
      - GPIO23
      net_scope: global
      no_connect: false
      connected_to:
      - reference: RPI1
        pin_number: '16'
        pin_name: GPIO23
    - number: '11'
      name: '11'
      electrical_type: passive
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      position:
        x: 172.72
        y: 99.06
      net: GPIO24
      net_aliases:
      - GPIO24
      net_scope: global
      no_connect: false
      connected_to:
      - reference: RPI1
        pin_number: '18'
        pin_name: GPIO24
    - number: '12'
      name: '12'
      electrical_type: passive
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      position:
        x: 172.72
        y: 101.6
      net: GPIO25
      net_aliases:
      - GPIO25
      net_scope: global
      no_connect: false
      connected_to:
      - reference: RPI1
        pin_number: '22'
        pin_name: GPIO25
    - number: '13'
      name: '13'
      electrical_type: passive
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      connected_to:
      - reference: RPI1
        pin_number: '19'
        pin_name: SPI_MOSI
    - number: '14'
      name: '14'
      electrical_type: passive
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      connected_to:
      - reference: RPI1
        pin_number: '21'
        pin_name: SPI_MISO
    - number: '15'
      name: '15'
      electrical_type: passive
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      connected_to:
      - reference: RPI1
        pin_number: '23'
        pin_name: SPI_SCLK
    - number: '16'
      name: '16'
      electrical_type: passive
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      connected_to:
      - reference: RPI1
        pin_number: '24'
        pin_name: '#SPI_CE0'
    - number: '17'
      name: '17'
      electrical_type: passive
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      connected_to:
      - reference: RPI1
        pin_number: '26'
        pin_name: '#SPI_CE1'
    - number: '18'
      name: '18'
      electrical_type: passive
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      position:
        x: 172.72
        y: 116.84
      net: GPIO5
      net_aliases:
      - GPIO5
      net_scope: global
      no_connect: false
      connected_to:
      - reference: RPI1
        pin_number: '29'
        pin_name: GPIO5
    - number: '19'
      name: '19'
      electrical_type: passive
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      position:
        x: 172.72
        y: 119.38
      net: GPIO6
      net_aliases:
      - GPIO6
      net_scope: global
      no_connect: false
      connected_to:
      - reference: RPI1
        pin_number: '31'
        pin_name: GPIO6
    - number: '20'
      name: '20'
      electrical_type: passive
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      position:
        x: 172.72
        y: 121.92
      net: GPIO12
      net_aliases:
      - GPIO12
      net_scope: global
      no_connect: false
      connected_to:
      - reference: RPI1
        pin_number: '32'
        pin_name: GPIO12
    - number: '21'
      name: '21'
      electrical_type: passive
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      position:
        x: 172.72
        y: 124.46
      net: GPIO13
      net_aliases:
      - GPIO13
      net_scope: global
      no_connect: false
      connected_to:
      - reference: RPI1
        pin_number: '33'
        pin_name: GPIO13
    - number: '22'
      name: '22'
      electrical_type: passive
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      position:
        x: 172.72
        y: 127.0
      net: GPIO16
      net_aliases:
      - GPIO16
      net_scope: global
      no_connect: false
      connected_to:
      - reference: RPI1
        pin_number: '36'
        pin_name: GPIO16
    - number: '23'
      name: '23'
      electrical_type: passive
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      position:
        x: 172.72
        y: 129.54
      net: GPIO19
      net_aliases:
      - GPIO19
      net_scope: global
      no_connect: false
      connected_to:
      - reference: RPI1
        pin_number: '35'
        pin_name: GPIO19
    - number: '24'
      name: '24'
      electrical_type: passive
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      position:
        x: 172.72
        y: 132.08
      net: GPIO20
      net_aliases:
      - GPIO20
      net_scope: global
      no_connect: false
      connected_to:
      - reference: RPI1
        pin_number: '38'
        pin_name: GPIO20
    - number: '25'
      name: '25'
      electrical_type: passive
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      position:
        x: 172.72
        y: 134.62
      net: GPIO21
      net_aliases:
      - GPIO21
      net_scope: global
      no_connect: false
      connected_to:
      - reference: RPI1
        pin_number: '40'
        pin_name: GPIO21
    size:
      local_graphics:
        measurement: symbol graphics only; excludes pins, properties, and text
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    pin_name: RXD
  - reference: RPI1
    pin_number: '11'
    pin_name: GPIO17
  - reference: RPI1
    pin_number: '12'
    pin_name: GPIO18
  - reference: RPI1
    pin_number: '13'
    pin_name: GPIO27
  - reference: RPI1
    pin_number: '15'
    pin_name: GPIO22
  - reference: RPI1
    pin_number: '16'
    pin_name: GPIO23
  - reference: RPI1
    pin_number: '18'
    pin_name: GPIO24
  - reference: RPI1
    pin_number: '19'
    pin_name: SPI_MOSI
  - reference: RPI1
    pin_number: '21'
    pin_name: SPI_MISO
  - reference: RPI1
    pin_number: '22'
    pin_name: GPIO25
  - reference: RPI1
    pin_number: '23'
    pin_name: SPI_SCLK
  - reference: RPI1
    pin_number: '24'
    pin_name: '#SPI_CE0'
  - reference: RPI1
    pin_number: '26'
    pin_name: '#SPI_CE1'
  - reference: RPI1
    pin_number: '29'
    pin_name: GPIO5
  - reference: RPI1
    pin_number: '3'
    pin_name: SDA
  - reference: RPI1
    pin_number: '31'
    pin_name: GPIO6
  - reference: RPI1
    pin_number: '32'
    pin_name: GPIO12
  - reference: RPI1
    pin_number: '33'
    pin_name: GPIO13
  - reference: RPI1
    pin_number: '35'
    pin_name: GPIO19
  - reference: RPI1
    pin_number: '36'
    pin_name: GPIO16
  - reference: RPI1
    pin_number: '38'
    pin_name: GPIO20
  - reference: RPI1
    pin_number: '40'
    pin_name: GPIO21
  - reference: RPI1
    pin_number: '5'
    pin_name: SCL
  - reference: RPI1
    pin_number: '7'
    pin_name: GPIO4
  - reference: RPI1
    pin_number: '8'
    pin_name: TXD
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    layers:
    - '*.Cu'
    - '*.Mask'
    net: GPIO4
    net_number: null
    pin_function: null
    pin_type: null
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    layers:
    - '*.Cu'
    - '*.Mask'
    net: GPIO17
    net_number: null
    pin_function: null
    pin_type: null
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    layers:
    - '*.Cu'
    - '*.Mask'
    net: GPIO18
    net_number: null
    pin_function: null
    pin_type: null
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    layers:
    - '*.Cu'
    - '*.Mask'
    net: GPIO27
    net_number: null
    pin_function: null
    pin_type: null
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    layers:
    - '*.Cu'
    - '*.Mask'
    net: GPIO22
    net_number: null
    pin_function: null
    pin_type: null
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    layers:
    - '*.Cu'
    - '*.Mask'
    net: GPIO23
    net_number: null
    pin_function: null
    pin_type: null
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    layers:
    - '*.Cu'
    - '*.Mask'
    net: GPIO24
    net_number: null
    pin_function: null
    pin_type: null
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    layers:
    - '*.Cu'
    - '*.Mask'
    net: GPIO25
    net_number: null
    pin_function: null
    pin_type: null
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    layers:
    - '*.Cu'
    - '*.Mask'
    net: GPIO5
    net_number: null
    pin_function: null
    pin_type: null
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    layers:
    - '*.Cu'
    - '*.Mask'
    net: GPIO6
    net_number: null
    pin_function: null
    pin_type: null
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    layers:
    - '*.Cu'
    - '*.Mask'
    net: GPIO12
    net_number: null
    pin_function: null
    pin_type: null
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    layers:
    - '*.Cu'
    - '*.Mask'
    net: GPIO13
    net_number: null
    pin_function: null
    pin_type: null
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    layers:
    - '*.Cu'
    - '*.Mask'
    net: GPIO16
    net_number: null
    pin_function: null
    pin_type: null
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    layers:
    - '*.Cu'
    - '*.Mask'
    net: GPIO19
    net_number: null
    pin_function: null
    pin_type: null
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

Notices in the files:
parts and their libraries:
microbuilder: This work is placed in the public domain, and may be freely used for commercial and non-commercial work with the following conditions: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
